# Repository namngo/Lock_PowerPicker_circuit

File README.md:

# Lock_PowerPicker_circuit
A circuit to automatically pick between wall-adapter or battery for the electronic lock.

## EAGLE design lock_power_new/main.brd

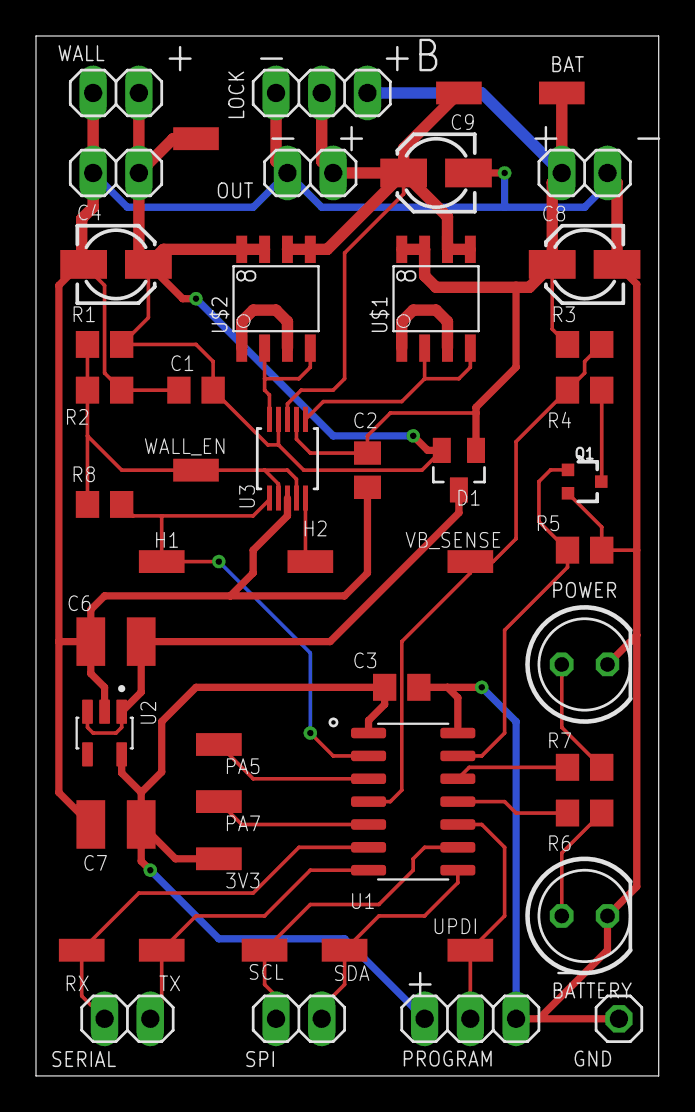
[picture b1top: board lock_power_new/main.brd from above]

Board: 2 copper layers, 34.6 x 57.8 mm, 49 parts (0 on the bottom side), 27 nets.

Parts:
3V3: SMD1,27-2,54
BAT: 1X02
BAT1: SMD1,27-2,54
BATTERY: LED5MM
C1, C2, C3: 0.1uf; C0805
C4, C8: 22uf; 153CLV-0405
C6, C7: 1uf; C1210
C9: 10uf; 153CLV-0405
D1: BAS70-05; SOT23
GND: 1X01
H1, H2: SMD1,27-2,54
LOCK: 1X03
OUT: 1X02
PA5, PA7: SMD1,27-2,54
POWER: LED5MM
PROGRAM: 1X03
Q1: 310mA/60V/1.6Ω; SOT323
R1, R3: 200k; R0805
R2: 45k; R0805
R4, R5: 100k; R0805
R6, R7: 65; R0805
R8: 1M; R0805
RX: SMD1,27-2,54
SCL: SMD1,27-2,54
SDA: SMD1,27-2,54
SERIAL: 1X02
SPI: 1X02
TX: SMD1,27-2,54
U1: ATTINY1614; SOIC127P600X175-14N
U2: RS3236-3.3; SOT95P285X140-5N
U3: LTC4416; MSOP-10_MS
U$1, U$2: IRF7314PBF; SO-8
UPDI: SMD1,27-2,54
VB_SENSE: SMD1,27-2,54
V_OUT: SMD1,27-2,54
WALL, WALL2: 1X02
WALL1: SMD1,27-2,54
WALL_EN: SMD1,27-2,54

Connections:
+3.3V: 3V3.1, C3.2, C7.1, PROGRAM.1, U1.1, U2.5
+7V: C1.1, C4.+, D1.2, R1.2, U3.9, U$2.7, U$2.8, WALL.1, WALL1.1, WALL2.1
+UB: BAT.1, BAT1.1, C2.2, C8.+, D1.1, LOCK.3, R3.1, U3.7, U$1.7, U$1.8
BEFORE_V: C6.1, D1.3, U2.1, U2.3
G1: U3.10, U$2.2, U$2.4
G2: U3.6, U$1.2, U$1.4
GND: BAT.2, BATTERY.K, C1.2, C2.1, C3.1, C4.-, C6.2, C7.2, C8.-, C9.-, GND.1, LOCK.1, OUT.2, POWER.K, PROGRAM.3, Q1.2, R2.1, R5.1, U1.14, U2.2, U3.3, WALL.2, WALL2.2
H1: H1.1, R8.2, U1.2, U3.1
LED1: R7.2, U1.12
LED2: R6.2, U1.11
unnamed: R3.2, R4.2, U1.4, VB_SENSE.1
unnamed: PA7.1, U1.5
unnamed: U$1.1, U$1.3
unnamed: U$2.1, U$2.3
unnamed: POWER.A, R7.1
unnamed: H2.1, U3.5
unnamed: Q1.3, R4.1
unnamed: PA5.1, U1.3
unnamed: BATTERY.A, R6.1
PA3: Q1.1, R5.2, U1.13
RX: RX.1, SERIAL.2, U1.6
SCL: SCL.1, SPI.2, U1.9
SDA: SDA.1, SPI.1, U1.8
TX: SERIAL.1, TX.1, U1.7
UPDI: PROGRAM.2, U1.10, UPDI.1
VOUT: C9.+, LOCK.2, OUT.1, U3.8, U$1.5, U$1.6, U$2.5, U$2.6, V_OUT.1
WALL_EN: R1.1, R2.2, R8.1, U3.2, U3.4, WALL_EN.1

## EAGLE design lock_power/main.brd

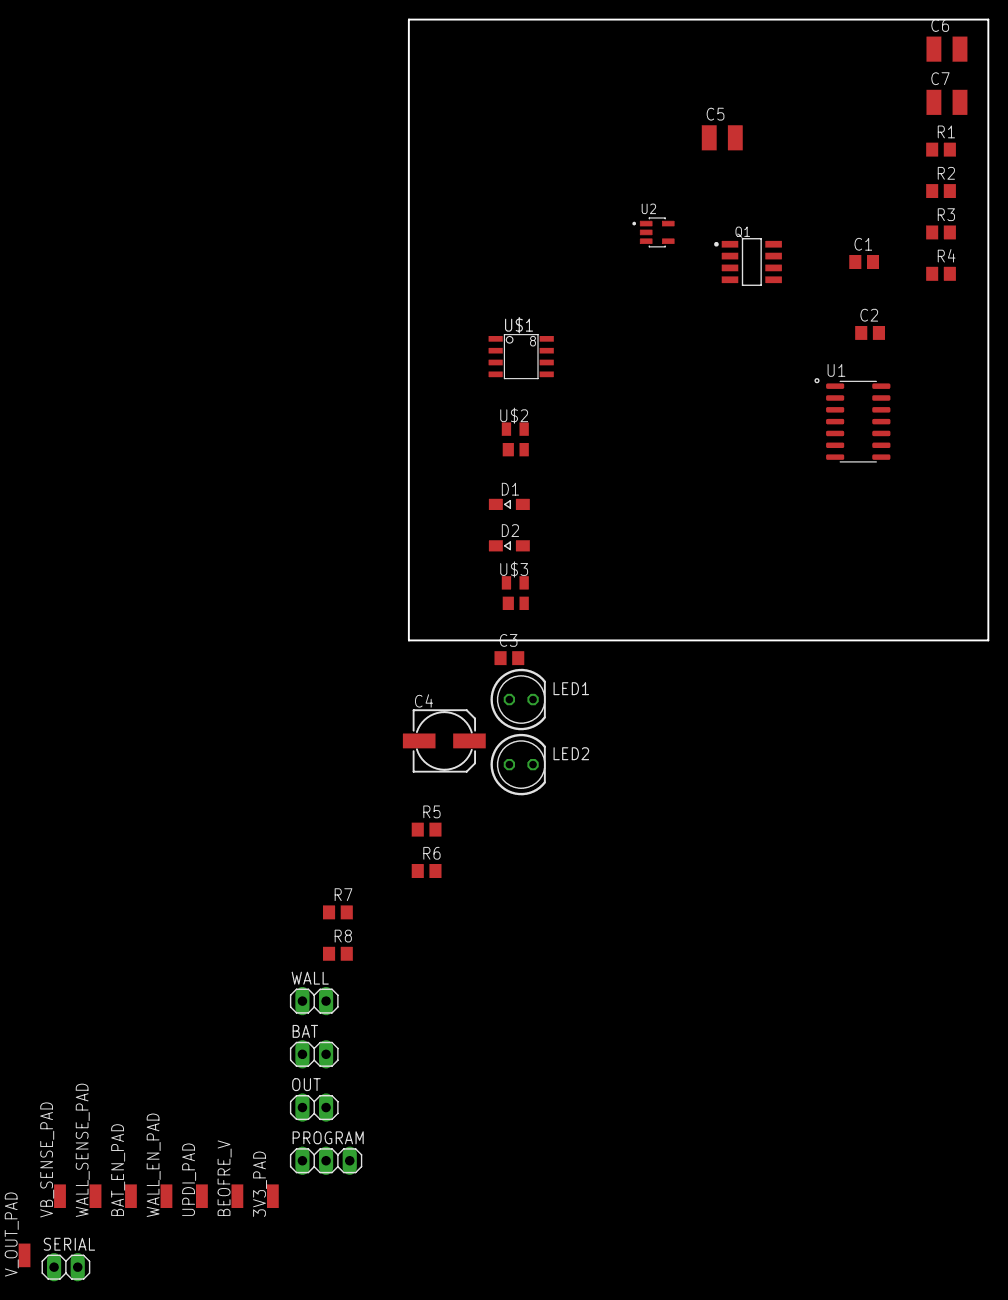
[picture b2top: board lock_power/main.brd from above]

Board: 2 copper layers, 62.2 x 66.7 mm, 38 parts (0 on the bottom side), 23 nets, no tracks yet.

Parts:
3V3_PAD: SMD1,27-2,54
BAT: 1X02
BAT_EN_PAD: SMD1,27-2,54
BEOFRE_V: SMD1,27-2,54
C1, C2, C3: 1nf; C0805
C4: 100uf; 153CLV-0605
C5, C6, C7: 1uf; C1210
D1, D2: SOD323-W
LED1, LED2: LED5MM
OUT: 1X02
PROGRAM: 1X03
Q1: j; INFINEON_IRF8910PBF_0
R1, R3: 200k; R0805
R2, R4, R7: 100k; R0805
R5, R6: 65; R0805
R8: 1k; R0805
SERIAL: 1X02
U1: ATTINY1614-SSNR; SOIC127P600X175-14N
U2: RS3236-3.3; SOT95P285X140-5N
U$1: IRF7314PBF; SO-8
U$2, U$3: MIC5018; SOT143
UPDI_PAD: SMD1,27-2,54
VB_SENSE_PAD: SMD1,27-2,54
V_OUT_PAD: SMD1,27-2,54
WALL: 1X02
WALL_EN_PAD: SMD1,27-2,54
WALL_SENSE_PAD: SMD1,27-2,54

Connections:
+3.3V: 3V3_PAD.1, C3.2, C7.1, PROGRAM.1, U1.1, U2.5
+7V: C1.1, C2.1, D1.A, Q1.3, R1.1, U$2.2, U$3.2, WALL.1
+UB: BAT.1, D2.A, R3.1, R7.1, U$1.5, U$1.6
BAT_EN: BAT_EN_PAD.1, R8.2, U1.11
GND: BAT.2, C1.2, C2.2, C3.1, C4.-, C5.2, C6.2, C7.2, OUT.2, PROGRAM.3, R2.1, R4.1, R5.1, R6.1, U1.14, U2.2, U$2.1, U$3.1, WALL.2
unnamed: BEOFRE_V.1, C6.1, D1.C, D2.C, U2.1, U2.3
unnamed: LED1.K, R5.2
unnamed: Q1.4, U$3.3
unnamed: Q1.2, U$2.3
unnamed: Q1.5, Q1.7
unnamed: Q1.6, Q1.8
unnamed: LED2.K, R6.2
unnamed: U$1.1, U$1.3
unnamed: R7.2, R8.1, U$1.2, U$1.4
unnamed: LED2.A, U1.8
unnamed: R1.2, R2.2, U1.2, WALL_SENSE_PAD.1
unnamed: R3.2, R4.2, U1.3, VB_SENSE_PAD.1
unnamed: LED1.A, U1.9
RX: SERIAL.2, U1.6
TX: SERIAL.1, U1.7
UPDI: PROGRAM.2, U1.10, UPDI_PAD.1
VOUT: C4.+, C5.1, OUT.1, Q1.1, U$1.7, U$1.8, V_OUT_PAD.1
WALL_EN: U1.12, U$2.4, U$3.4, WALL_EN_PAD.1

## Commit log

2022-10-25 initial kicad design
2022-10-25 half finish schematic
2022-10-26 finish schematic, moving to pcb
2022-10-27 ready to pcb
2022-10-27 remove kicad files
2022-10-27 add ealge files
2022-10-28 add the lp38693
2022-10-28 almost done
2022-10-28 finish sch
2022-10-30 finish the board
2022-10-30 ignore files
2022-10-30 done
2022-11-10 generate files
2023-01-02 finish chip version
2023-01-02 new board
2023-01-04 add back the driver
2023-01-06 finish board

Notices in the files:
parts and their libraries:
SparkFun-DiscreteSemi: Licensing: Creative Commons ShareAlike 4.0 International - https://creativecommons.org/licenses/by-sa/4.0
